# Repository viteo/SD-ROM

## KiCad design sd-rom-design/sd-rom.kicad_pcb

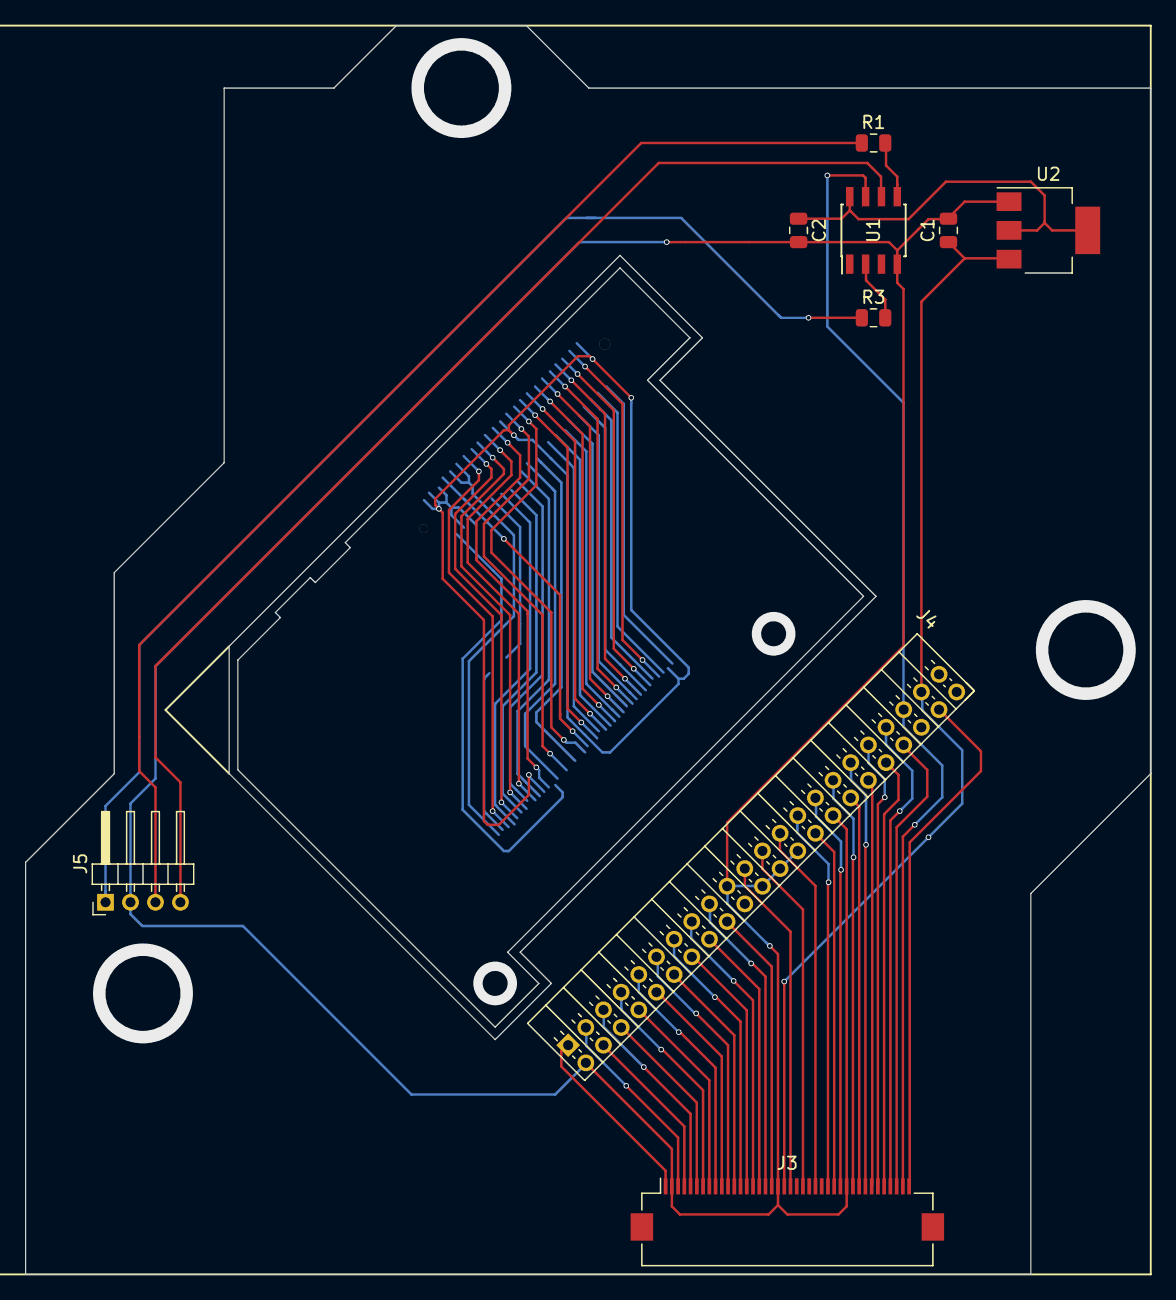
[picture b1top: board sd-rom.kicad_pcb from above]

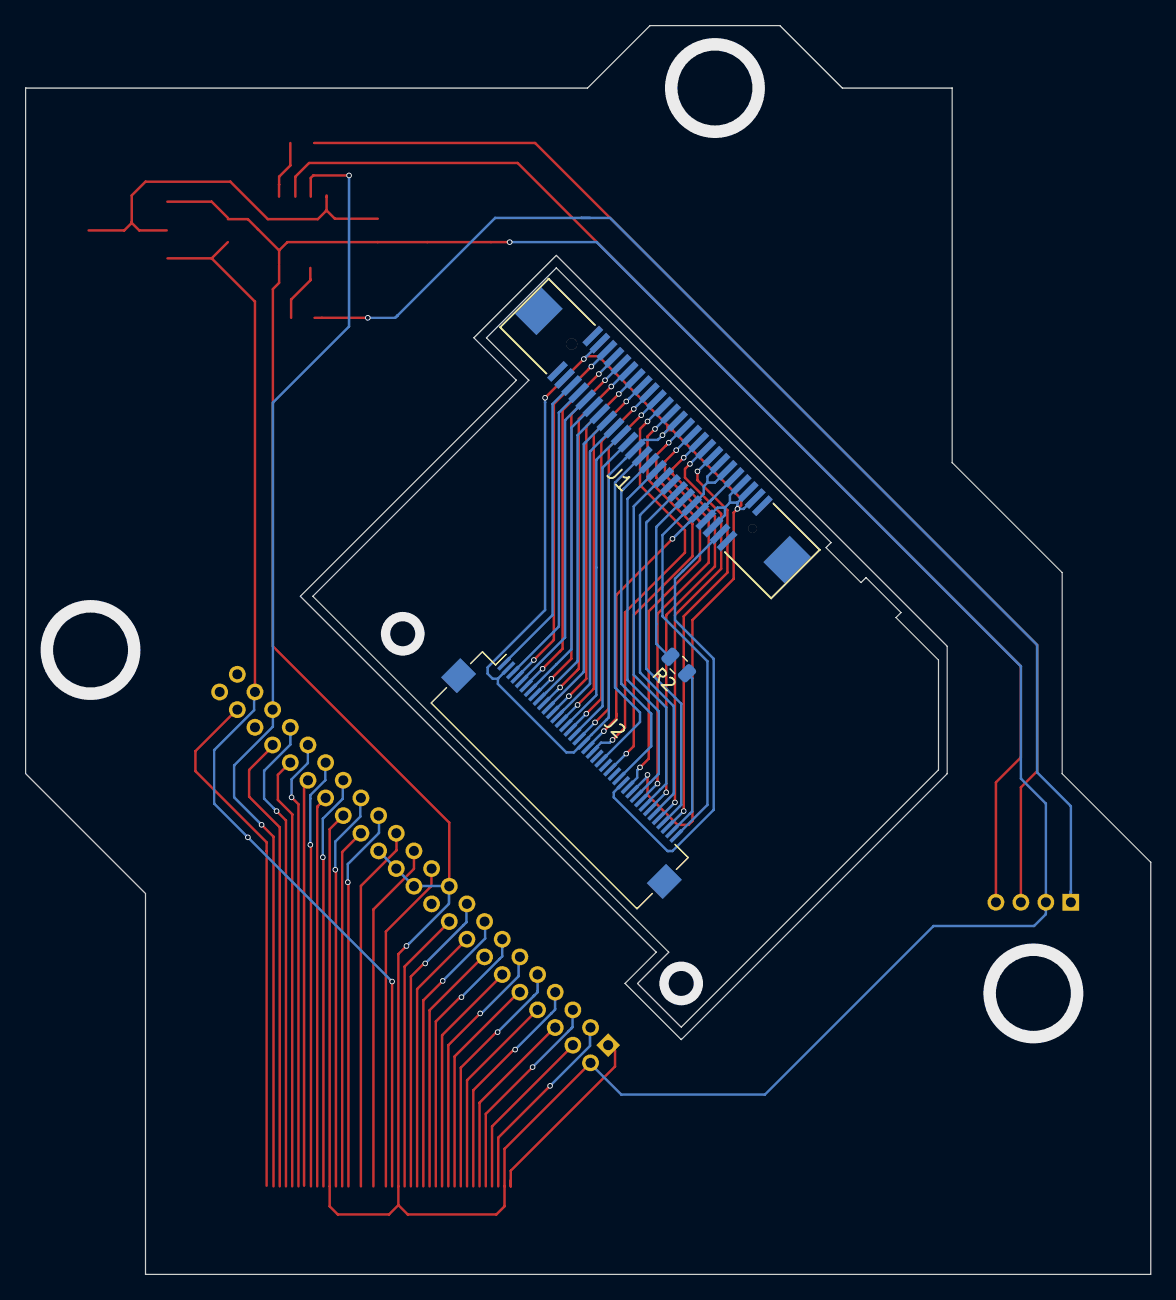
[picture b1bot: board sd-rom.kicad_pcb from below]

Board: 2 copper layers, 90.1 x 100.0 mm, 12 parts (3 on the bottom side), 77 nets.

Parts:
C1: 10; C_0805_2012Metric
C2: 100; C_0805_2012Metric
J1: JAE50
J2, J3: Conn_01x40; Hirose_FH12-40S-0.5SH_1x40-1MP_P0.50mm_Horizontal
J4: SD44; PinSocket_2x22_P2.00mm_Horizontal
J5: Conn_01x04_Male; PinHeader_1x04_P2.00mm_Horizontal
R1, R3: 300; R_0805_2012Metric
R2: 0; R_0805_2012Metric
U1: ATtiny13A-SSU; SOIC-8_3.9x4.9mm_P1.27mm
U2: AMS1117-3.3; SOT-223-3_TabPin2

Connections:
/Button: J5.4, U1.6
/LedIn: J3.39, J4.39, U1.7
/LedOut: R1.2, U1.5
/Motor: R3.2, U1.2
GND: C1.2, C2.2, J3.2, J3.19, J3.30, J4.2, J4.19, J4.22, J4.24, J4.26, J4.30, J5.2, U1.4, U2.1
GNDREF: J1.4, J1.23, J1.26, J1.43, J1.44, J1.45, J1.46, J1.48, J2.2, J2.19, J2.30
unnamed: C2.1, U1.8, U2.2
unnamed: J1.5, J2.1
unnamed: J1.6, J2.4
unnamed: J1.7, J2.3
unnamed: J1.8, J2.6
unnamed: J1.9, J2.5
unnamed: J1.10, J2.8
unnamed: J1.11, J2.7
unnamed: J1.12, J2.10
unnamed: J1.13, J2.9
unnamed: J1.14, J2.12
unnamed: J1.15, J2.11
unnamed: J1.16, J2.14
unnamed: J1.17, J2.13
unnamed: J1.18, J2.16
unnamed: J1.19, J2.15
unnamed: J1.20, J2.18
unnamed: J1.21, J2.17
unnamed: J1.22, J2.21
unnamed: J1.24, J2.25
unnamed: J1.25, J2.23
unnamed: J1.27, J2.27
unnamed: J1.28, J2.29
unnamed: J1.29, J2.31
unnamed: J1.30, J2.32
unnamed: J1.31, J2.33
unnamed: J1.32, J2.34
unnamed: J1.33, J2.35
unnamed: J1.34, J2.36
unnamed: J1.35, J2.37
unnamed: J1.36, J2.38
unnamed: J1.37, R2.2
unnamed: J1.38, J1.39, J1.40, J2.40
unnamed: J1.41, J1.42, J2.20
unnamed: J1.47, J2.28
unnamed: J2.39, R2.1
unnamed: J3.1, J4.1
unnamed: J3.3, J4.3
unnamed: J3.4, J4.4
unnamed: J3.5, J4.5
unnamed: J3.6, J4.6
unnamed: J3.7, J4.7
unnamed: J3.8, J4.8
unnamed: J3.9, J4.9
unnamed: J3.10, J4.10
unnamed: J3.11, J4.11
unnamed: J3.12, J4.12
unnamed: J3.13, J4.13
unnamed: J3.14, J4.14
unnamed: J3.15, J4.15
unnamed: J3.16, J4.16
unnamed: J3.17, J4.17
unnamed: J3.18, J4.18
unnamed: J3.21, J4.21
unnamed: J3.23, J4.23
unnamed: J3.25, J4.25
unnamed: J3.27, J4.27
unnamed: J3.28, J4.28
unnamed: J3.29, J4.29
unnamed: J3.31, J4.31
unnamed: J3.32, J4.32
unnamed: J3.33, J4.33
unnamed: J3.34, J4.34
unnamed: J3.35, J4.35
unnamed: J3.36, J4.36
unnamed: J3.37, J4.37
unnamed: J3.38, J4.38
unnamed: J3.40, J4.42
unnamed: J5.1, R3.1
unnamed: J5.3, R1.1
VCC: C1.1, J3.20, J4.41, U2.3

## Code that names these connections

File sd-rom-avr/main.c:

#define F_CPU 1000000UL
#include <avr/io.h>
#include <avr/interrupt.h>
#include <util/delay.h>

#define LEDIN 0
#define LEDOUT 2
#define MOTOR 3

ISR(INT0_vect)
{
	{
	_delay_ms(1000); //blinking here
	}
	PORTB |= (1 << MOTOR) | (1 << LEDOUT);
	_delay_ms(30);
	PORTB &= ~(1 << MOTOR) & ~(1 << LEDOUT);
}

int main(void)
{
	GIMSK |= (1 << INT0); //INT0 interrupt  on bit PB1
	MCUCR |= (1 << ISC01); //falling edge
	sei();
	DDRB = 0b1100;	// 0 - IDE PIN 39 - LED INPUT
					// 1 - SD-ROM BUTTON EJECT (INTERRUPT)
					// 2 - LED INDICATOR
					// 3 - MOTOR
	PORTB = 0b000010;

	while (1)
	{
		if (PINB & (1 << LEDIN))
		{
			PORTB &= ~(1 << LEDOUT);
		}
		else
		{
			PORTB |= (1 << LEDOUT);
		}
	}
}

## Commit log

2018-10-29 second board dimensions
2018-11-01 board variant 1
2018-11-01 board variant 2
2018-11-01 attiny added to schema
2018-11-02 power stabilizer added
2018-11-02 schema update
2018-11-05 mcu logic
2018-11-05 schema fix
2018-11-05 kicad project moved to a folder
2018-11-08 board variant 3
2018-11-09 parts found in local shop
2018-12-22 tracing in progress
2019-02-07 pcb design finished
